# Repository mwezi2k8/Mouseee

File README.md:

# Mouseee
custom mouse with all the design amd code

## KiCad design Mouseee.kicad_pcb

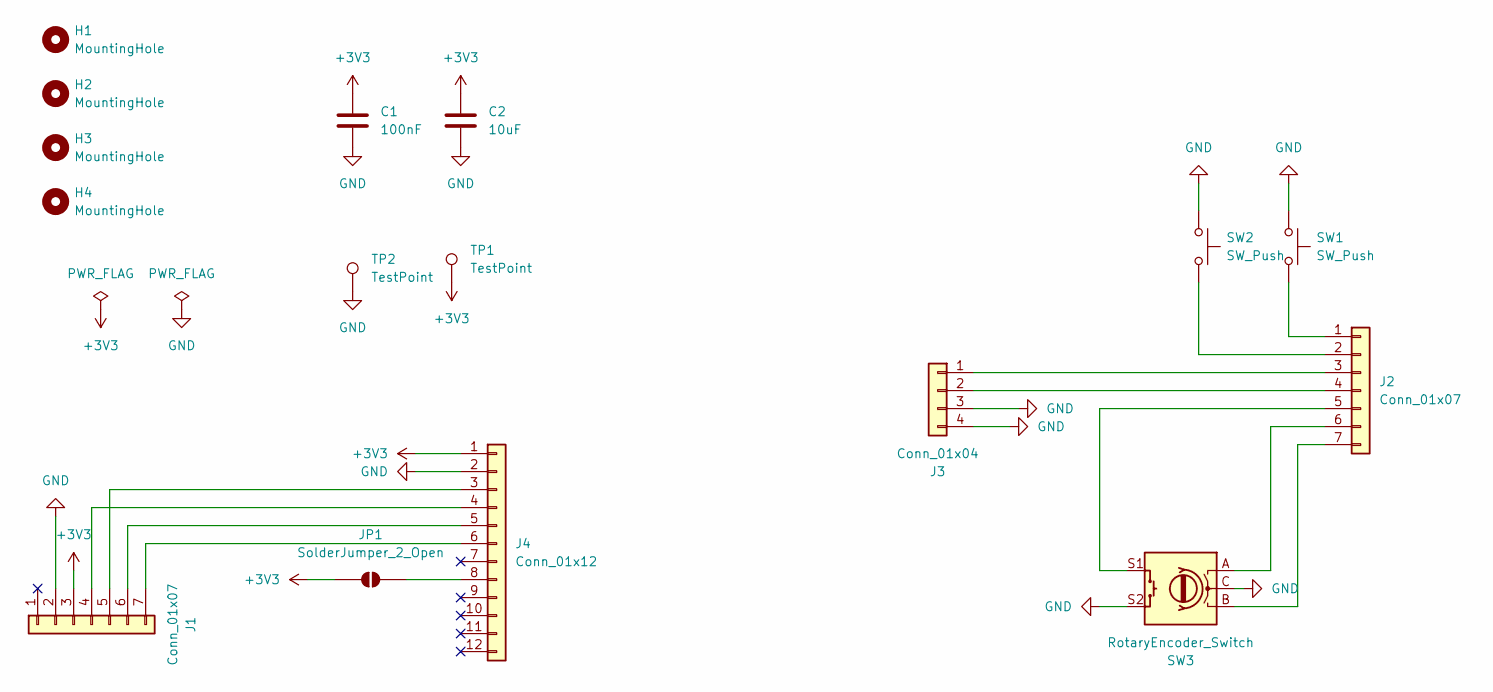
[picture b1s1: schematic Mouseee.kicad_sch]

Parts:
C1: 100nF; C_0805_2012Metric
C2: 10uF; C_0805_2012Metric
H1, H2, H3, H4: MountingHole; MountingHole_2.2mm_M2
J1, J2: Conn_01x07; PinSocket_1x07_P2.54mm_Vertical
J3: Conn_01x04; PinHeader_1x04_P2.54mm_Vertical
J4: Conn_01x12; PinSocket_1x12_P2.54mm_Vertical
JP1: SolderJumper_2_Open; SolderJumper-2_P1.3mm_Open_RoundedPad1.0x1.5mm
SW1, SW2: SW_Push; MouseSwitch_Omron_D2FC-F-7N
SW3: RotaryEncoder_Switch; RotaryEncoder_Alps_EC11E-Switch_Vertical_H20mm
TP1, TP2: TestPoint; TestPoint_Pad_D1.5mm

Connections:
+3V3: C1.1, C2.1, J1.3, J4.1, JP1.1 (A), TP1.1 (1_1)
GND: C1.2, C2.2, J1.2, J3.3, J3.4, J4.2, SW1.2, SW2.2, SW3.C, SW3.S2, TP2.1 (1_1)
unnamed: J1.4, J4.4
unnamed: J1.5, J4.3
unnamed: J1.6, J4.5
unnamed: J1.7, J4.6
unnamed: J2.1, SW1.1
unnamed: J2.2, SW2.1
unnamed: J2.3, J3.1
unnamed: J2.4, J3.2
unnamed: J2.5, SW3.S1
unnamed: J2.6, SW3.A
unnamed: J2.7, SW3.B
unnamed: J4.8, JP1.2 (B)

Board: 2 copper layers, 16 parts (0 on the bottom side), 14 nets, no tracks yet.
